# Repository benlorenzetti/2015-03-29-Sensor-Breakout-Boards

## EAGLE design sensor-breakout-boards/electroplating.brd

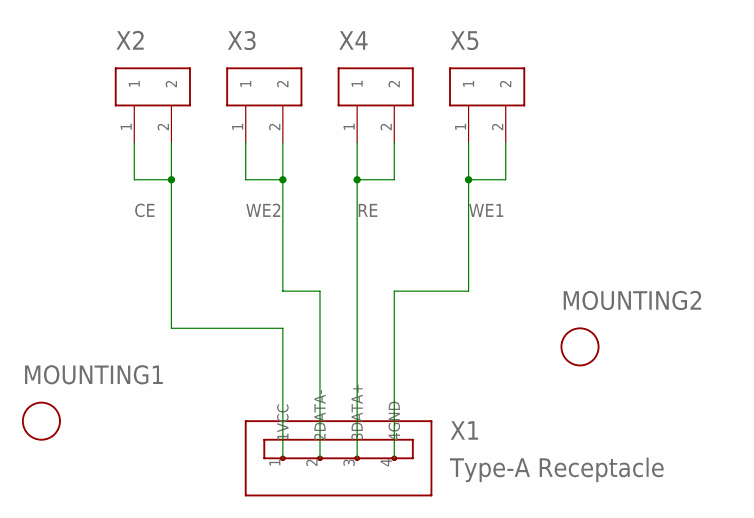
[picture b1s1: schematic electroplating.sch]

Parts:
MOUNTING1, MOUNTING2: M2-MOUNTING-HOLE
X1: Type-A Receptacle; TE_CONNECTIVITY_292303-1
X2, X3, X4, X5: 2-PIN-CONNECTOR; 2-PIN-HEADER

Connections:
CE: X1.1 (1VCC), X2.1, X2.2
RE: X1.3 (3DATA+), X4.1, X4.2
WE1: X1.4 (4GND), X5.1, X5.2
WE2: X1.2 (2DATA-), X3.1, X3.2

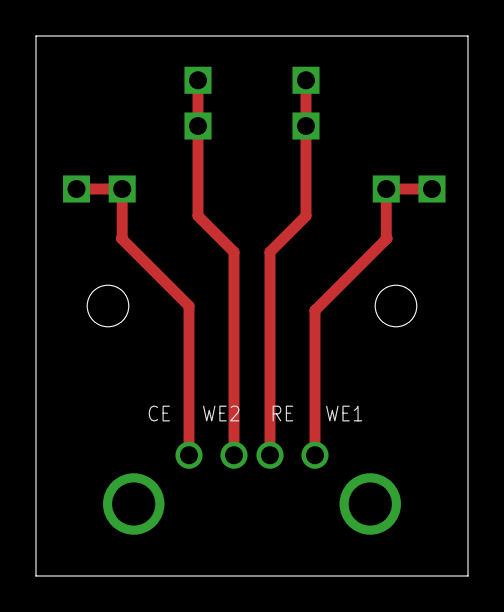
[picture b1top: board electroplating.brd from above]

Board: 2 copper layers, 24.0 x 30.0 mm, 7 parts (0 on the bottom side), 4 nets.

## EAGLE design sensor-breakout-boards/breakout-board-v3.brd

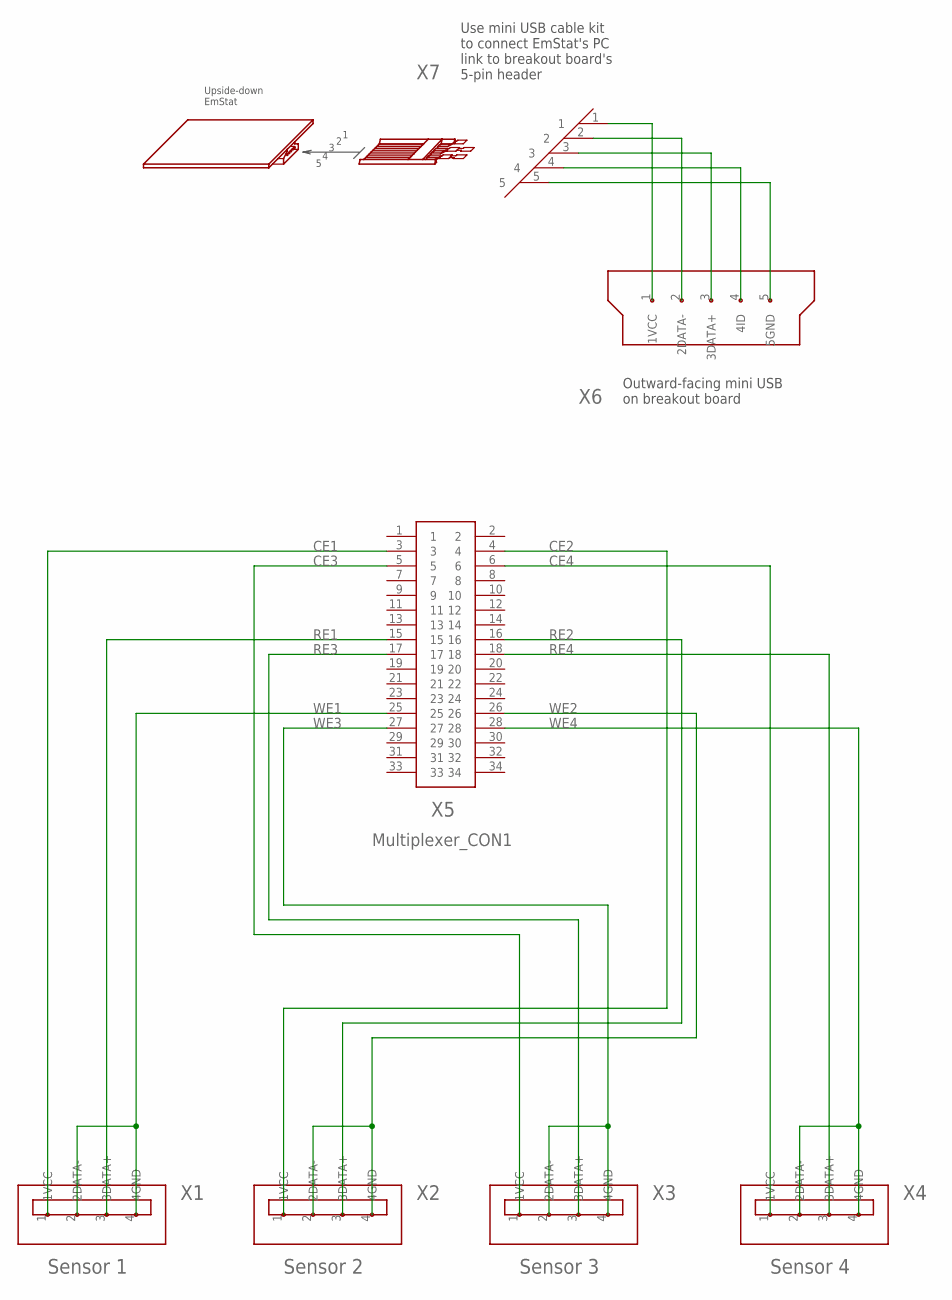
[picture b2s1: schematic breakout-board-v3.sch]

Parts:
X1: Sensor 1; TE_CONNECTIVITY_292303-1
X2: Sensor 2; TE_CONNECTIVITY_292303-1
X3: Sensor 3; TE_CONNECTIVITY_292303-1
X4: Sensor 4; TE_CONNECTIVITY_292303-1
X5: Multiplexer_CON1; SULLINS_SFH11-PBPC-D17-ST-BK
X6: USB-MICRO-TYPE-B-RECEPTACLE; MOLEX_0548190519
X7: EMSTAT-USB-CABLE; 5-PIN-HEADER

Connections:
CE1: X1.1 (1VCC), X5.3
CE2: X2.1 (1VCC), X5.4
CE3: X3.1 (1VCC), X5.5
CE4: X4.1 (1VCC), X5.6
D+: X6.3 (3DATA+), X7.3
D-: X6.2 (2DATA-), X7.2
GND: X5.11, X5.12, X5.23, X5.24, X5.33, X5.34, X6.5 (5GND), X7.5
ID: X6.4 (4ID), X7.4
RE1: X1.3 (3DATA+), X5.15
RE2: X2.3 (3DATA+), X5.16
RE3: X3.3 (3DATA+), X5.17
RE4: X4.3 (3DATA+), X5.18
VCC: X6.1 (1VCC), X7.1
WE1: X1.2 (2DATA-), X1.4 (4GND), X5.25
WE2: X2.2 (2DATA-), X2.4 (4GND), X5.26
WE3: X3.2 (2DATA-), X3.4 (4GND), X5.27
WE4: X4.2 (2DATA-), X4.4 (4GND), X5.28

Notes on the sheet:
Use mini USB cable kit to connect EmStat's PC link to breakout board's 5-pin header
Outward-facing mini USB on breakout board

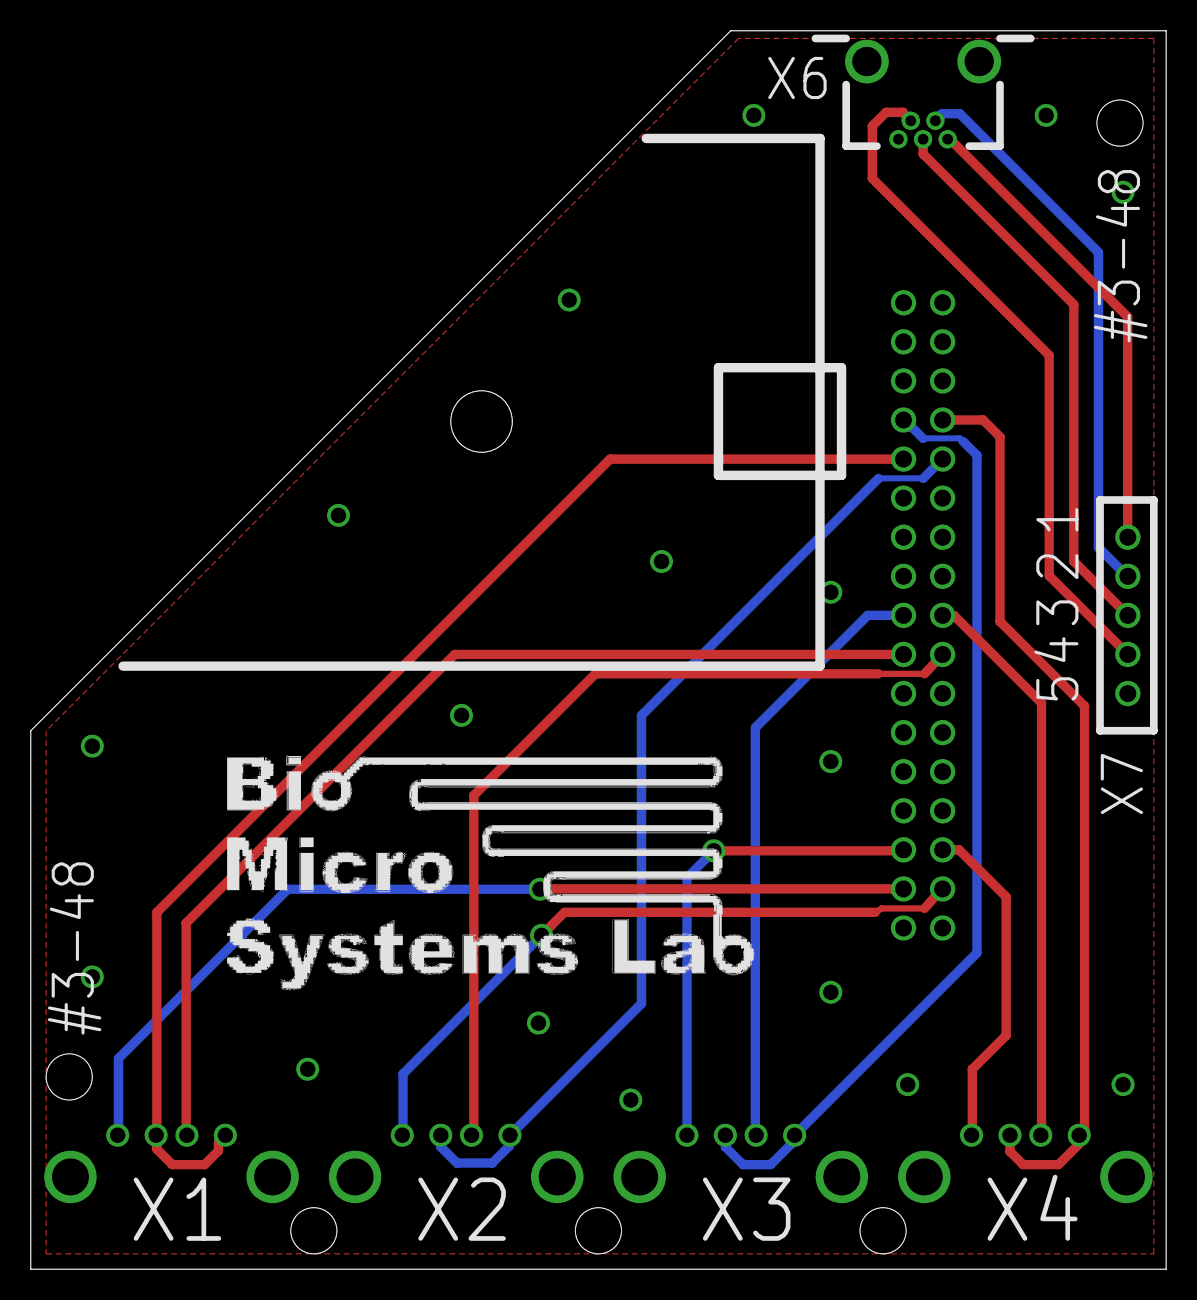
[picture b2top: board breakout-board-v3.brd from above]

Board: 2 copper layers, 73.8 x 80.5 mm, 7 parts (1 on the bottom side), 17 nets.

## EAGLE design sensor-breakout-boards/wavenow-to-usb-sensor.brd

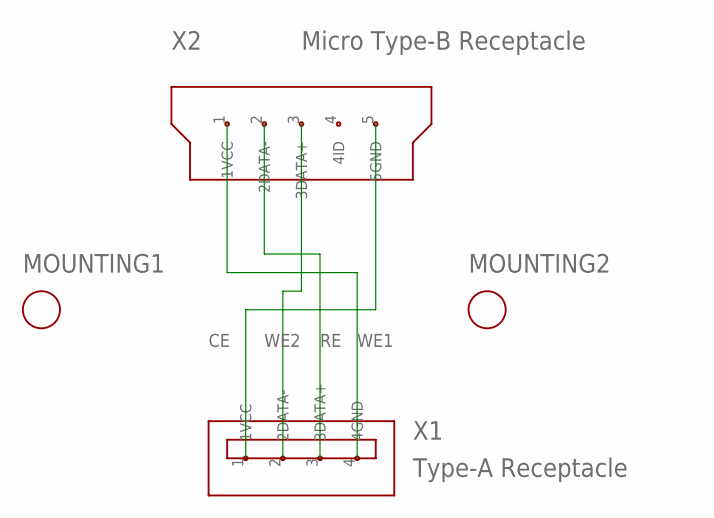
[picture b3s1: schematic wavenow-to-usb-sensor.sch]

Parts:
MOUNTING1, MOUNTING2: M2-MOUNTING-HOLE
X1: Type-A Receptacle; TE_CONNECTIVITY_292303-1
X2: Micro Type-B Receptacle; MOLEX_0548190519

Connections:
CE: X1.1 (1VCC), X2.5 (5GND)
RE: X1.3 (3DATA+), X2.2 (2DATA-)
WE1: X1.4 (4GND), X2.1 (1VCC)
WE2: X1.2 (2DATA-), X2.3 (3DATA+)

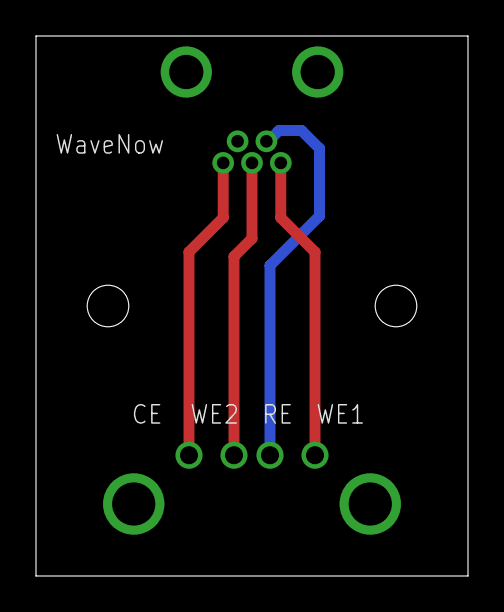
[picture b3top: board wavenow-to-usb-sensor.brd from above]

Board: 2 copper layers, 24.0 x 30.0 mm, 4 parts (0 on the bottom side), 4 nets.

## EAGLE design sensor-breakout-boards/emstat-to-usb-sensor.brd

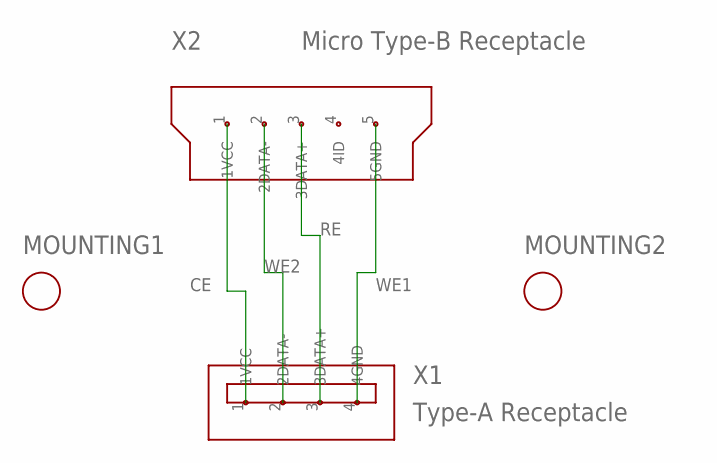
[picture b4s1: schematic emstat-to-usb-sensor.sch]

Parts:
MOUNTING1, MOUNTING2: M2-MOUNTING-HOLE
X1: Type-A Receptacle; TE_CONNECTIVITY_292303-1
X2: Micro Type-B Receptacle; MOLEX_0548190519

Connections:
CE: X1.1 (1VCC), X2.1 (1VCC)
RE: X1.3 (3DATA+), X2.3 (3DATA+)
WE1: X1.4 (4GND), X2.5 (5GND)
WE2: X1.2 (2DATA-), X2.2 (2DATA-)

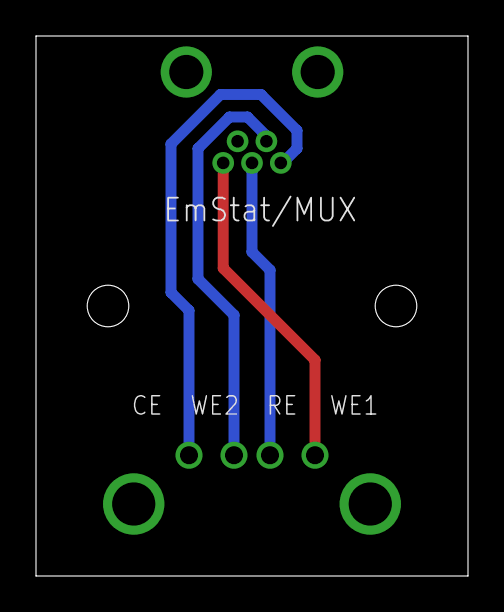
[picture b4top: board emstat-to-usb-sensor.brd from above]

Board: 2 copper layers, 24.0 x 30.0 mm, 4 parts (0 on the bottom side), 4 nets.

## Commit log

2015-04-01 usb pads
2015-04-01 emstat-to-usb-schematic
2015-04-01 three breakout boards complete
2015-04-01 fixed dotPng
2015-04-01 made changes discussed at meeting
2015-04-01 changed to 2.3mm clearance holes for M2 screws
2015-04-01 corrected wavenow-to-usb connections
2015-04-04 emstat-micro-type-b-plug-schematic
2015-04-06 breakout board schematic
2015-04-06 silkscreen layers added except for logo bitmap
2015-04-06 added BMS logo
2015-04-06 board complete
2015-04-09 added ground planes
2015-04-09 edited electroplating board per Prof. Pap.
